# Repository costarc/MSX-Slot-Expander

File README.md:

# MSX-Slot-Expander

Based in this project:  https://msxvillage.fr/forum/topic-881-17+slot-expander.php

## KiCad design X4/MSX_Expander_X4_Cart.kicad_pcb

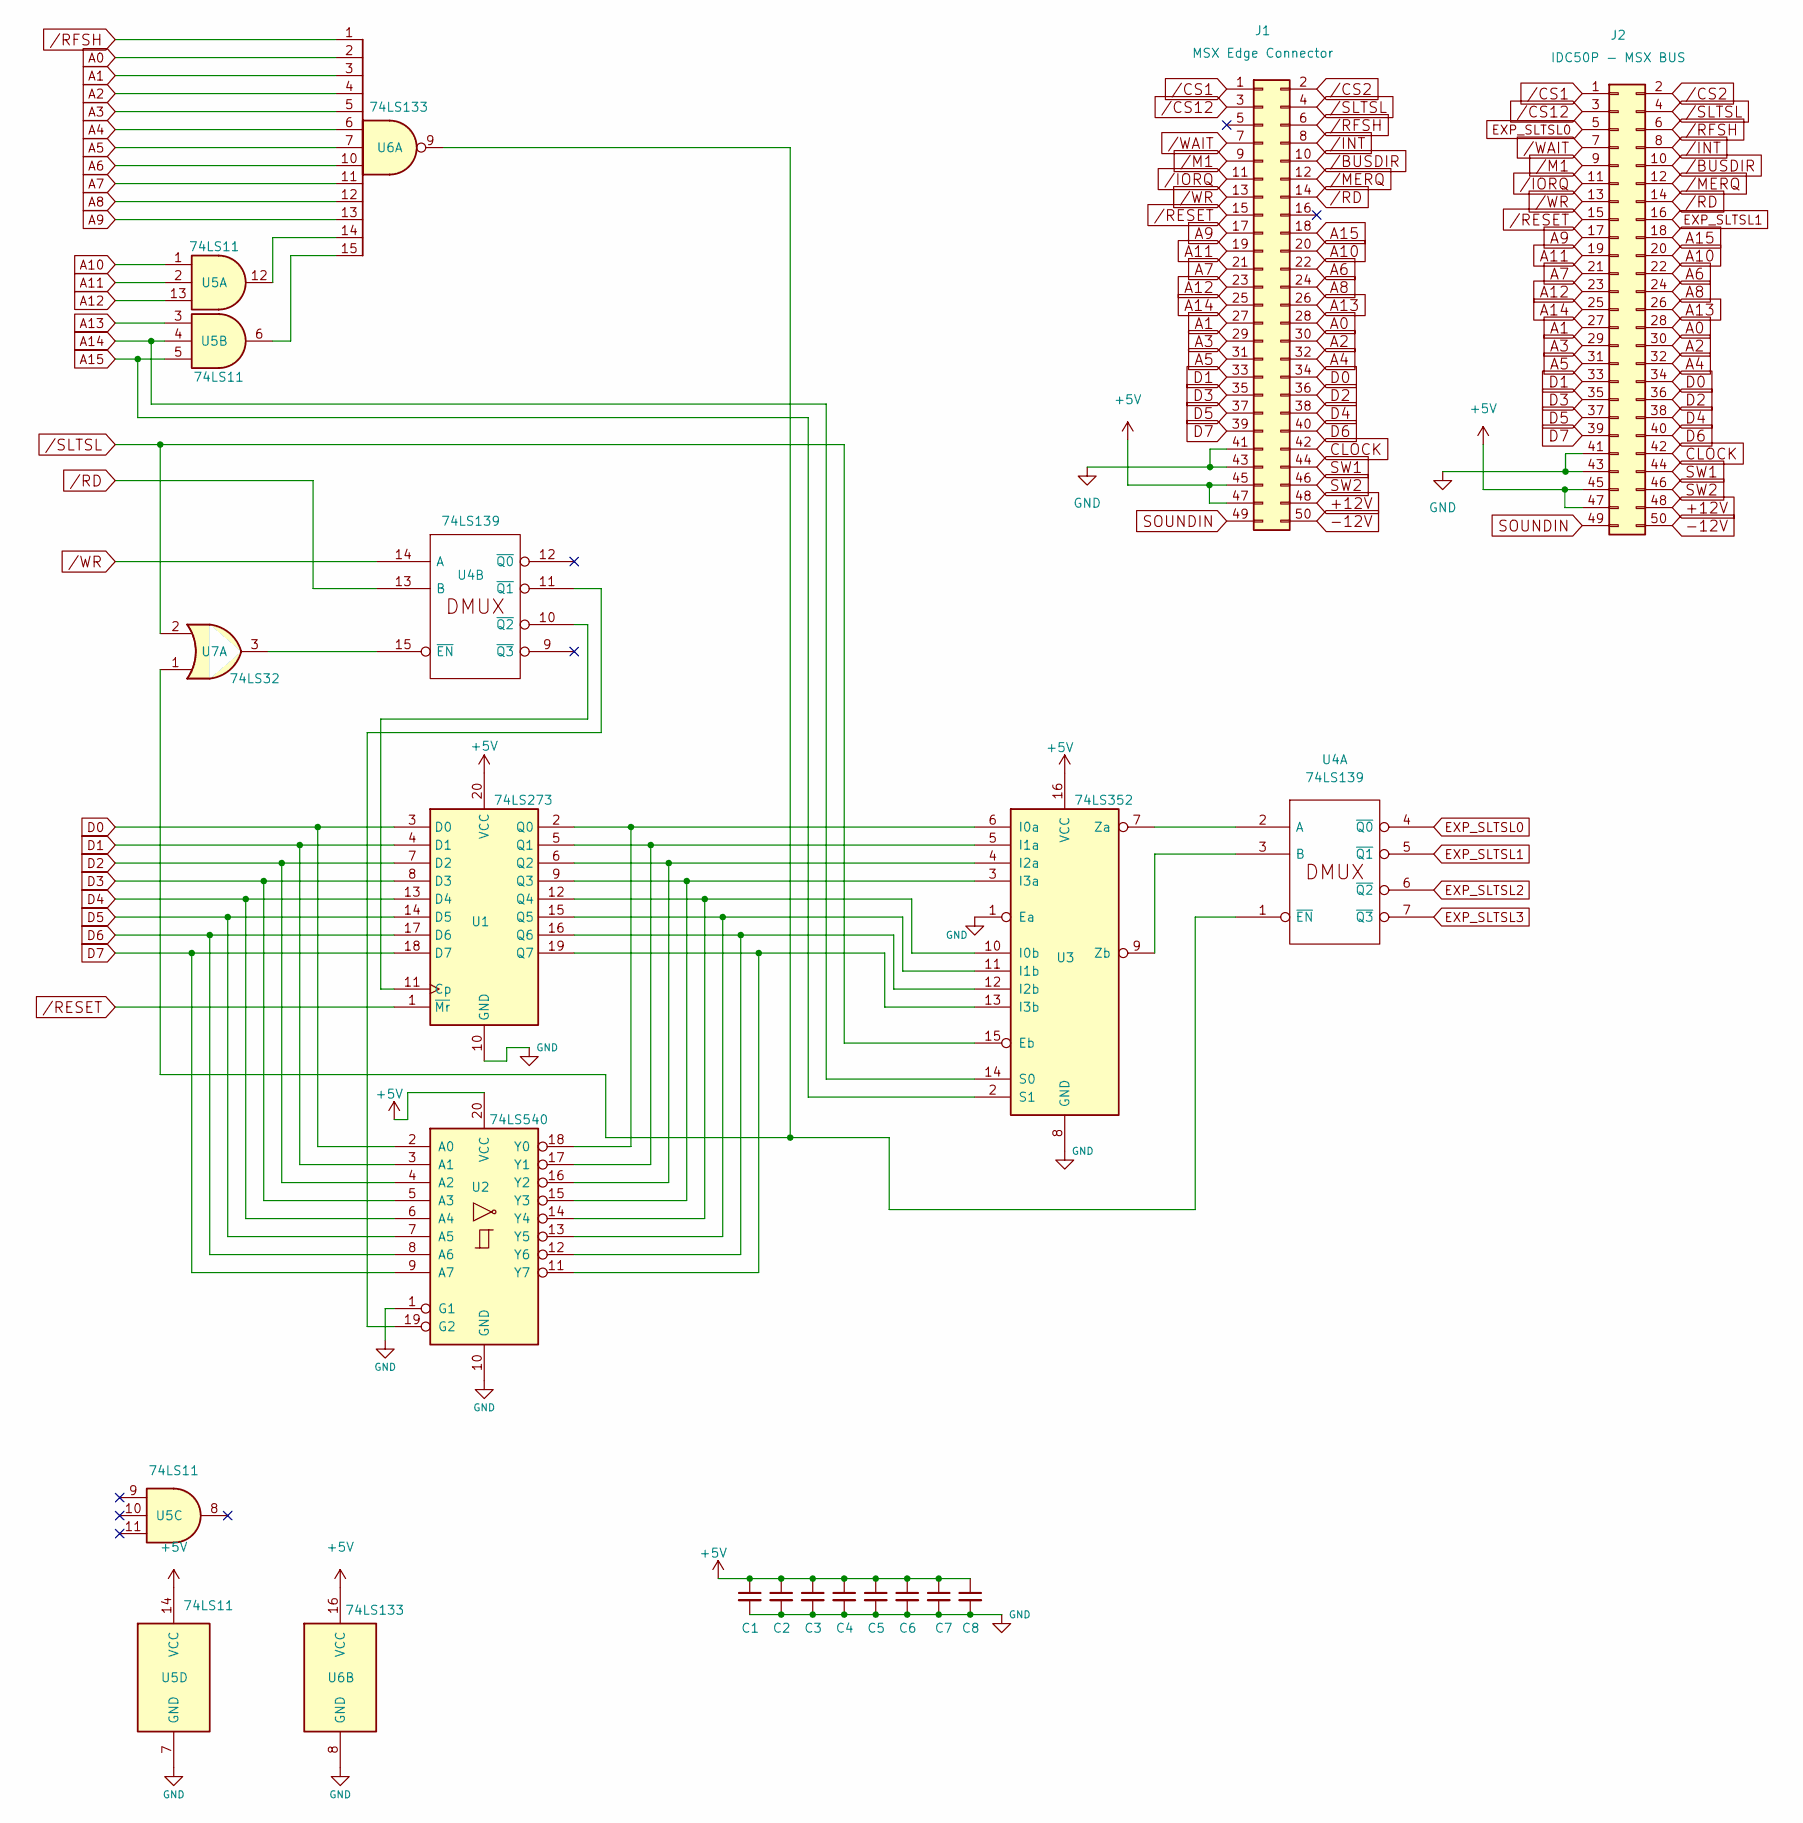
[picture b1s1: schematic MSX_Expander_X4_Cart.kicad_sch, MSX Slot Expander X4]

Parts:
C1, C2, C3, C4, C5, C6, C7, C8: 0.1; C_Disc_D5.0mm_W2.5mm_P5.00mm
J1: MSX Edge Connector; MSX_CART_SW_Official
J2: IDC50P - MSX BUS; IDC-Header_2x25_P2.54mm_Vertical
U1: 74LS273; DIP-20_W7.62mm
U2: 74LS540; DIP-20_W7.62mm
U3: 74LS352; DIP-16_W7.62mm
U4: 74LS139; DIP-16_W7.62mm
U5: 74LS11; DIP-14_W7.62mm
U6: 74LS133; DIP-16_W7.62mm
U7: 74LS32; DIP-14_W7.62mm

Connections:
+5V: C1.1, C2.1, C3.1, C4.1, C5.1, C6.1, C7.1, C8.1, J1.45, J1.47, J2.45, J2.47, U1.20 (VCC), U2.20 (VCC), U3.16 (VCC), U5.14 (VCC), U6.16 (VCC)
+12V: J1.48, J2.48
-12V: J1.50, J2.50
A0: J1.28, J2.28, U6.2
A1: J1.27, J2.27, U6.3
A2: J1.30, J2.30, U6.4
A3: J1.29, J2.29, U6.5
A4: J1.32, J2.32, U6.6
A5: J1.31, J2.31, U6.7
A6: J1.22, J2.22, U6.10
A7: J1.21, J2.21, U6.11
A8: J1.24, J2.24, U6.12
A9: J1.17, J2.17, U6.13
A10: J1.20, J2.20, U5.1
A11: J1.19, J2.19, U5.2
A12: J1.23, J2.23, U5.13
A13: J1.26, J2.26, U5.3
A14: J1.25, J2.25, U3.14 (S0), U5.4
A15: J1.18, J2.18, U3.2 (S1), U5.5
CLOCK: J1.42, J2.42
D0: J1.34, J2.34, U1.3 (D0), U2.2 (A0)
D1: J1.33, J2.33, U1.4 (D1), U2.3 (A1)
D2: J1.36, J2.36, U1.7 (D2), U2.4 (A2)
D3: J1.35, J2.35, U1.8 (D3), U2.5 (A3)
D4: J1.38, J2.38, U1.13 (D4), U2.6 (A4)
D5: J1.37, J2.37, U1.14 (D5), U2.7 (A5)
D6: J1.40, J2.40, U1.17 (D6), U2.8 (A6)
D7: J1.39, J2.39, U1.18 (D7), U2.9 (A7)
EXP_SLTSL0: J2.5, U4.4 (~Q0)
EXP_SLTSL1: J2.16, U4.5 (~Q1)
EXP_SLTSL2: U4.6 (~Q2)
EXP_SLTSL3: U4.7 (~Q3)
GND: C1.2, C2.2, C3.2, C4.2, C5.2, C6.2, C7.2, C8.2, J1.41, J1.43, J2.41, J2.43, U1.10 (GND), U2.1 (G1), U2.10 (GND), U3.1 (Ea), U3.8 (GND), U4.8 (GND), U5.7 (GND), U6.8 (GND)
unnamed: U1.2 (Q0), U2.18 (Y0), U3.6 (I0a)
unnamed: U1.5 (Q1), U2.17 (Y1), U3.5 (I1a)
unnamed: U1.6 (Q2), U2.16 (Y2), U3.4 (I2a)
unnamed: U1.9 (Q3), U2.15 (Y3), U3.3 (I3a)
unnamed: U1.11 (Cp), U4.10 (~Q2)
unnamed: U1.12 (Q4), U2.14 (Y4), U3.10 (I0b)
unnamed: U1.15 (Q5), U2.13 (Y5), U3.11 (I1b)
unnamed: U1.16 (Q6), U2.12 (Y6), U3.12 (I2b)
unnamed: U1.19 (Q7), U2.11 (Y7), U3.13 (I3b)
unnamed: U2.19 (G2), U4.11 (~Q1)
unnamed: U3.7 (Za), U4.2 (A)
unnamed: U3.9 (Zb), U4.3 (B)
unnamed: U4.1 (~EN), U6.9, U7.1
unnamed: U4.15 (~EN), U7.3
unnamed: U5.6, U6.15
unnamed: U5.12, U6.14
SOUNDIN: J1.49, J2.49
SW1: J1.44, J2.44
SW2: J1.46, J2.46
VCC: U4.16 (VCC)
/BUSDIR: J1.10, J2.10
/CS1: J1.1, J2.1
/CS2: J1.2, J2.2
/CS12: J1.3, J2.3
/INT: J1.8, J2.8
/IORQ: J1.11, J2.11
/M1: J1.9, J2.9
/MERQ: J1.12, J2.12
/RD: J1.14, J2.14, U4.13 (B)
/RESET: J1.15, J2.15, U1.1 (~Mr)
/RFSH: J1.6, J2.6, U6.1
/SLTSL: J1.4, J2.4, U3.15 (Eb), U7.2
/WAIT: J1.7, J2.7
/WR: J1.13, J2.13, U4.14 (A)

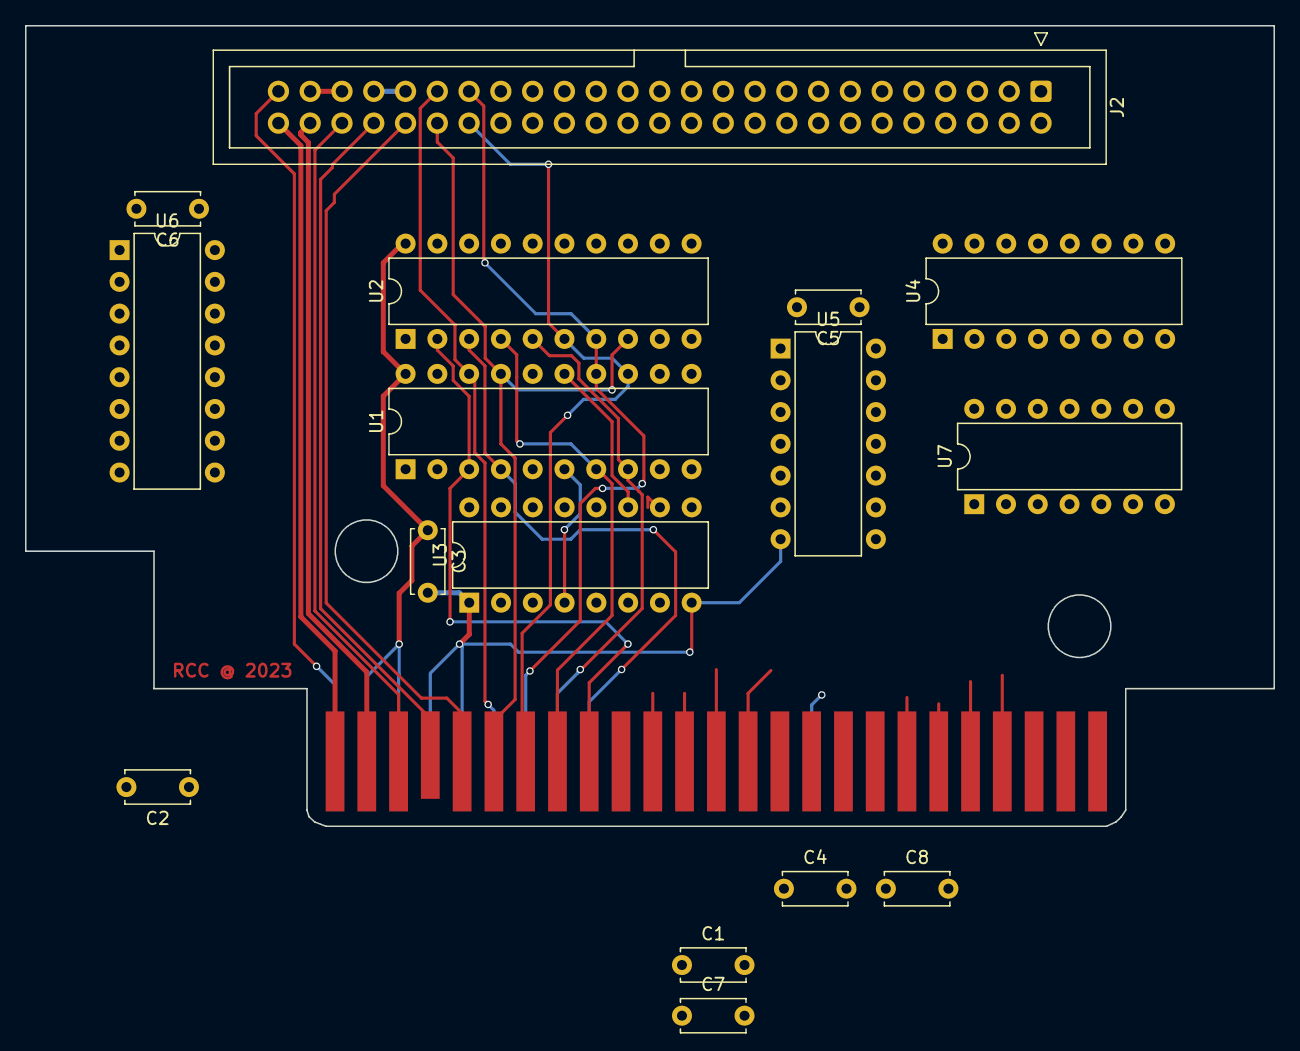
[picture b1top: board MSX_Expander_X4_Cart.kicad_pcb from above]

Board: 2 copper layers, 99.8 x 64.0 mm, 17 parts (0 on the bottom side), 64 nets.

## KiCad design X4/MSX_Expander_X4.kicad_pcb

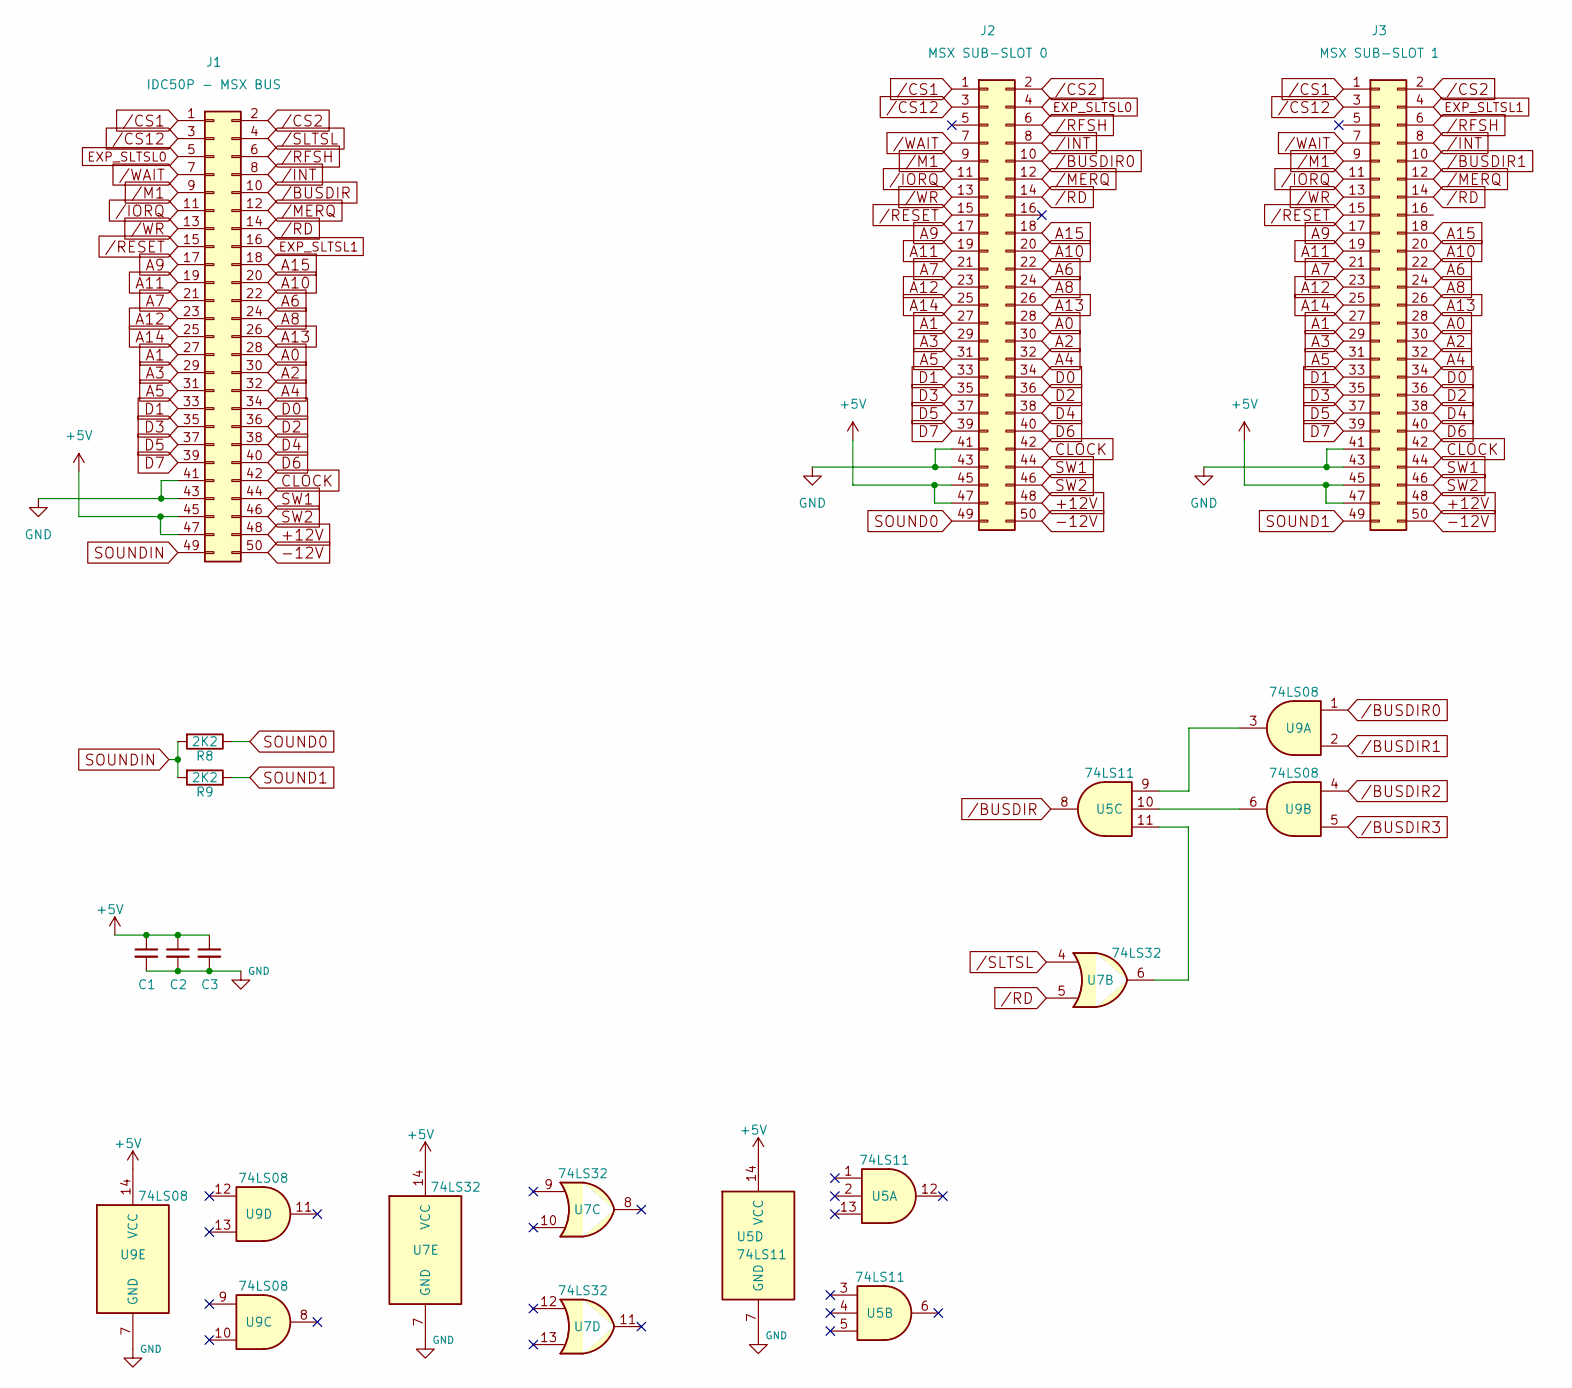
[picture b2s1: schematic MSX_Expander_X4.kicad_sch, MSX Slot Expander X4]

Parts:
C1, C2, C3: 0.1; C_Disc_D5.0mm_W2.5mm_P5.00mm
J1: IDC50P - MSX BUS; IDC-Header_2x25_P2.54mm_Vertical
J2: MSX SUB-SLOT 0; 50_pin_edge_female
J3: MSX SUB-SLOT 1; 50_pin_edge_female
R8, R9: 2K2; R_Axial_DIN0207_L6.3mm_D2.5mm_P7.62mm_Horizontal
U5: 74LS11; DIP-14_W7.62mm
U7: 74LS32; DIP-14_W7.62mm
U9: 74LS08; DIP-14_W7.62mm

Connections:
+5V: C1.1, C2.1, C3.1, J1.45, J1.47, J2.45, J2.47, J3.45, J3.47, U5.14 (VCC), U7.14 (VCC), U9.14 (VCC)
+12V: J1.48, J2.48, J3.48
-12V: J1.50, J2.50, J3.50
A0: J1.28, J2.28, J3.28
A1: J1.27, J2.27, J3.27
A2: J1.30, J2.30, J3.30
A3: J1.29, J2.29, J3.29
A4: J1.32, J2.32, J3.32
A5: J1.31, J2.31, J3.31
A6: J1.22, J2.22, J3.22
A7: J1.21, J2.21, J3.21
A8: J1.24, J2.24, J3.24
A9: J1.17, J2.17, J3.17
A10: J1.20, J2.20, J3.20
A11: J1.19, J2.19, J3.19
A12: J1.23, J2.23, J3.23
A13: J1.26, J2.26, J3.26
A14: J1.25, J2.25, J3.25
A15: J1.18, J2.18, J3.18
CLOCK: J1.42, J2.42, J3.42
D0: J1.34, J2.34, J3.34
D1: J1.33, J2.33, J3.33
D2: J1.36, J2.36, J3.36
D3: J1.35, J2.35, J3.35
D4: J1.38, J2.38, J3.38
D5: J1.37, J2.37, J3.37
D6: J1.40, J2.40, J3.40
D7: J1.39, J2.39, J3.39
EXP_SLTSL0: J1.5, J2.4
EXP_SLTSL1: J1.16, J3.4
GND: C1.2, C2.2, C3.2, J1.41, J1.43, J2.41, J2.43, J3.41, J3.43, U5.7 (GND), U7.7 (GND), U9.7 (GND)
unnamed: U5.9, U9.3
unnamed: U5.10, U9.6
unnamed: U5.11, U7.6
SOUND0: J2.49, R8.1
SOUND1: J3.49, R9.1
SOUNDIN: J1.49, R8.2, R9.2
SW1: J1.44, J2.44, J3.44
SW2: J1.46, J2.46, J3.46
/BUSDIR: J1.10, U5.8
/BUSDIR0: J2.10, U9.1
/BUSDIR1: J3.10, U9.2
/BUSDIR2: U9.4
/BUSDIR3: U9.5
/CS1: J1.1, J2.1, J3.1
/CS2: J1.2, J2.2, J3.2
/CS12: J1.3, J2.3, J3.3
/INT: J1.8, J2.8, J3.8
/IORQ: J1.11, J2.11, J3.11
/M1: J1.9, J2.9, J3.9
/MERQ: J1.12, J2.12, J3.12
/RD: J1.14, J2.14, J3.14, U7.5
/RESET: J1.15, J2.15, J3.15
/RFSH: J1.6, J2.6, J3.6
/SLTSL: J1.4, U7.4
/WAIT: J1.7, J2.7, J3.7
/WR: J1.13, J2.13, J3.13

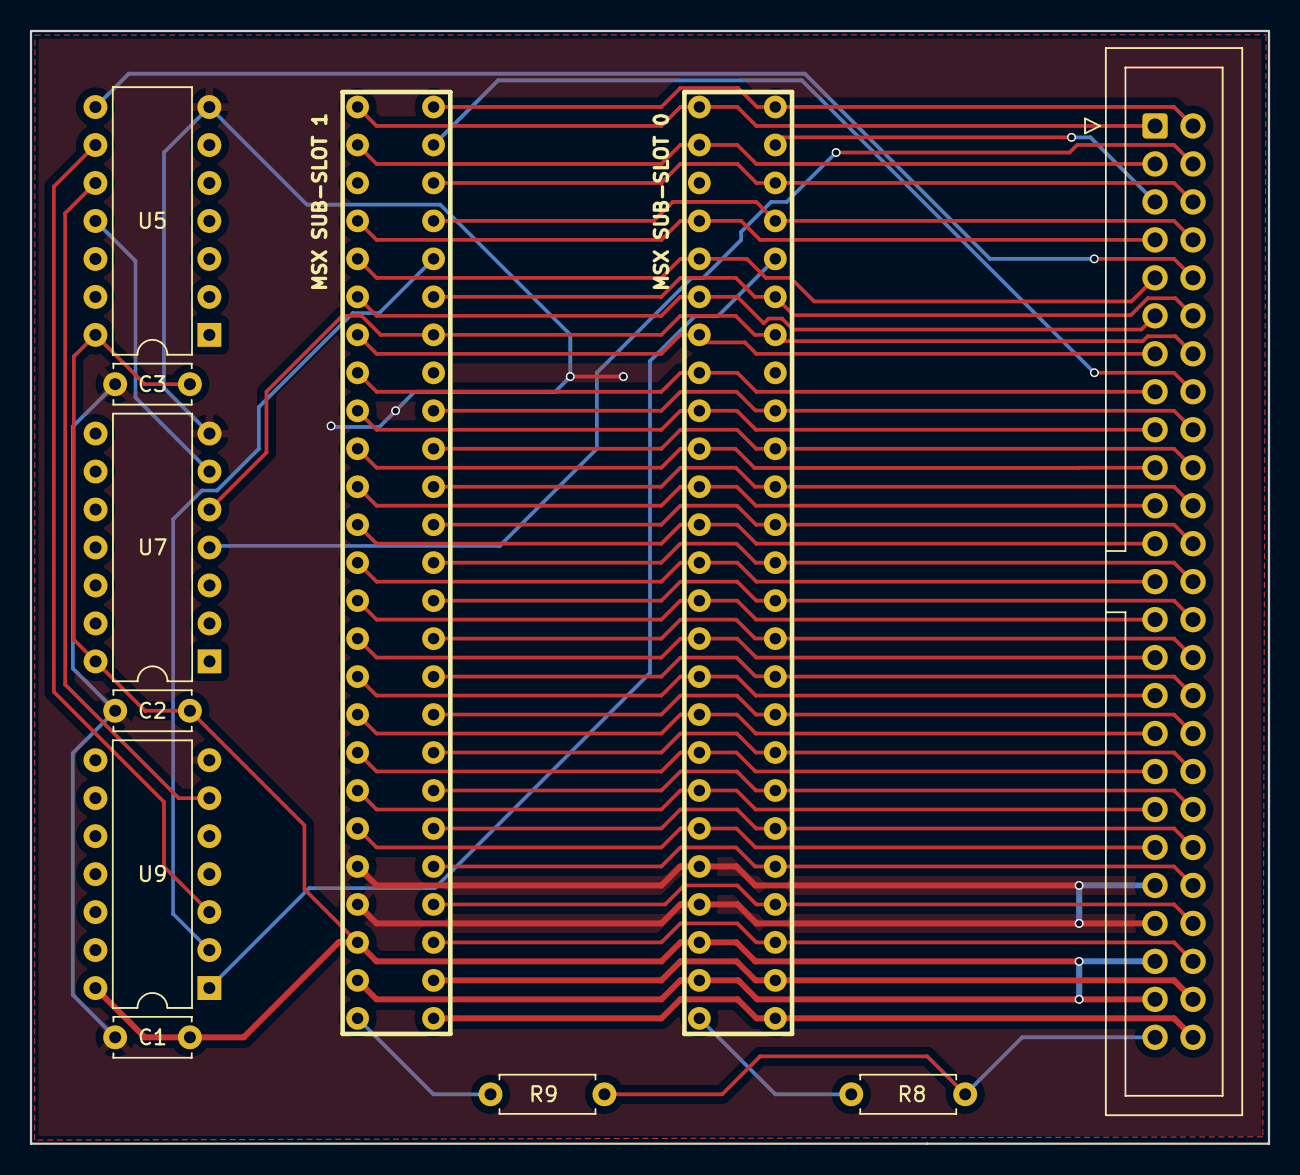
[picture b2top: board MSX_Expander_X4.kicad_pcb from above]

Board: 2 copper layers, 82.8 x 74.4 mm, 11 parts (0 on the bottom side), 55 nets.

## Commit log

2023-02-23 Added README
2023-02-23 Added schema for Expander X4
2023-02-23 added png of original X4 schema
2023-02-24 routing pcb
2023-03-08 started routing
